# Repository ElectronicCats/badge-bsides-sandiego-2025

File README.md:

# Badge bsides San Diego 2025

## Technology

- CH32V003
- LEDs
- Display OLED
- 2x AAA Battery Holder
- Shitty Addon Connector

## Gratitude
Do you want to say thank you? Tag these companies on social networks and show them your badge, thanks to them it is possible

- [ElectronicCats](https://electroniccats.com/)
- [BsidesSanDiego](https://www.bsidessd.org/)

## License

Electronic Cats invests time and resources providing this open source design, please support Electronic Cats and open-source hardware by purchasing products from Electronic Cats!

Designed by Electronic Cats.

Hardware released under an CERN Open Hardware Licence v1.2. See the LICENSE_HARDWARE file for more information.

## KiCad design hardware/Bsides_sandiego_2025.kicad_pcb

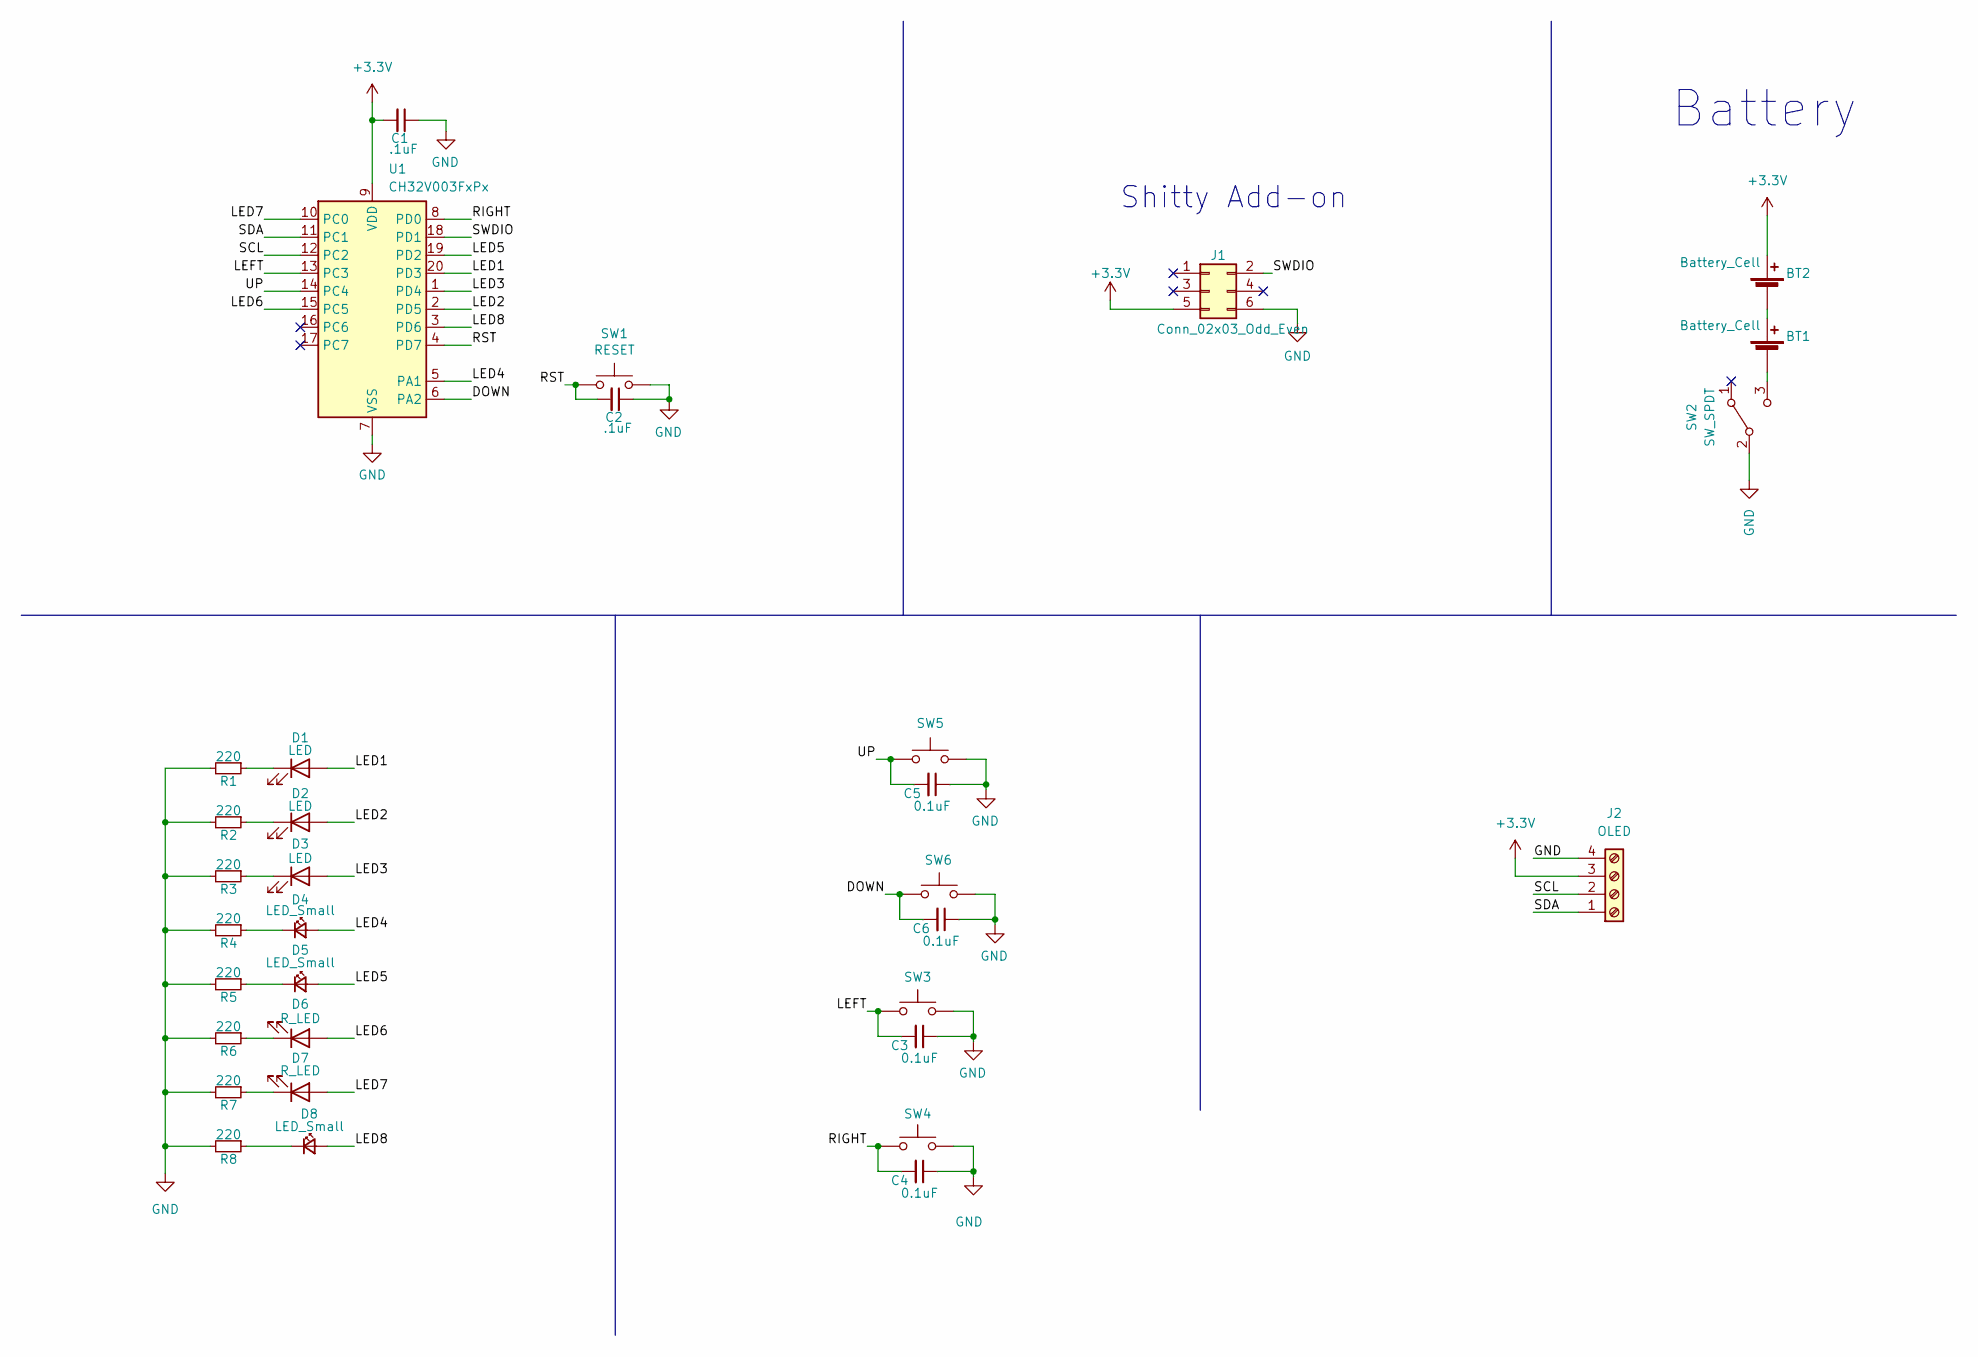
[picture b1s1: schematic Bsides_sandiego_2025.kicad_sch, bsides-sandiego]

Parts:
BT1, BT2: Battery_Cell; BatteryHolder_Keystone_2466_1xAAA; LCSC# C5290189
C1, C2: .1uF; C_0603_1608Metric; LCSC# C478888
C3, C4, C5, C6: 0.1uF; C_0603_1608Metric; LCSC# C478888
D1: LED; LED_0201_0603Metric; LCSC# C5440628
D2: LED; LED_0402_1005Metric; LCSC# C434450
D3: LED; LED_0603_1608Metric; LCSC# C434424
D4, D5: LED_Small; LED_S; LCSC# C2886268
D6, D7: R_LED; LYT77K-K2M1
D8: LED_Small; Led_S_S; LCSC# C409795
J1: Conn_02x03_Odd_Even; PinHeader_2x03_P2.54mm_Vertical_SMD; LCSC# C124390
J2: OLED; Display OLED 128 x32
R1, R2, R3, R4, R5, R6, R7, R8: 220; R_0603_1608Metric; LCSC# C22962
SW1: RESET; SW_SPST_TL3342; LCSC# C318889
SW2: SW_SPDT; MSK12C02; LCSC# C431540
SW3, SW4, SW5, SW6: SW_SPST_TL3342; LCSC# C318889
U1: CH32V003FxPx; TSSOP-20_4.4x6.5mm_P0.65mm; LCSC# C5187096

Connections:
+3.3V: BT2.2 (+), C1.2, J1.5, J2.3, U1.9 (VDD)
/DOWN: C6.2, SW6.2, U1.6 (PA2)
/LED1: D1.2 (A), U1.20 (PD3)
/LED2: D2.2 (A), U1.2 (PD5)
/LED3: D3.2 (A), U1.1 (PD4)
/LED4: D4.2 (A), U1.5 (PA1)
/LED5: D5.2 (A), U1.19 (PD2)
/LED6: D6.2 (A), U1.15 (PC5)
/LED7: D7.2 (A), U1.10 (PC0)
/LED8: D8.2 (A), U1.3 (PD6)
/LEFT: C3.2, SW3.2, U1.13 (PC3)
/RIGHT: C4.2, SW4.2, U1.8 (PD0)
/RST: C2.2, SW1.2, U1.4 (PD7)
/SCL: J2.2, U1.12 (PC2)
/SDA: J2.1, U1.11 (PC1)
/SWDIO: J1.2, U1.18 (PD1)
/UP: C5.2, SW5.2, U1.14 (PC4)
GND: C1.1, C2.1, C3.1, C4.1, C5.1, C6.1, J1.6, J2.4, R1.2, R2.2, R3.2, R4.2, R5.2, R6.2, R7.2, R8.2, SW1.1, SW2.2 (B), SW3.1, SW4.1, SW5.1, SW6.1, U1.7 (VSS)
unnamed: BT1.2 (+), BT2.1 (-)
unnamed: BT1.1 (-), SW2.3 (C)
unnamed: D1.1 (K), R1.1
unnamed: D2.1 (K), R2.1
unnamed: D3.1 (K), R3.1
unnamed: D4.1 (K), R4.1
unnamed: D5.1 (K), R5.1
unnamed: D6.1 (K), R6.1
unnamed: D7.1 (K), R7.1
unnamed: D8.1 (K), R8.1

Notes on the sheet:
Shitty Add-on
Battery

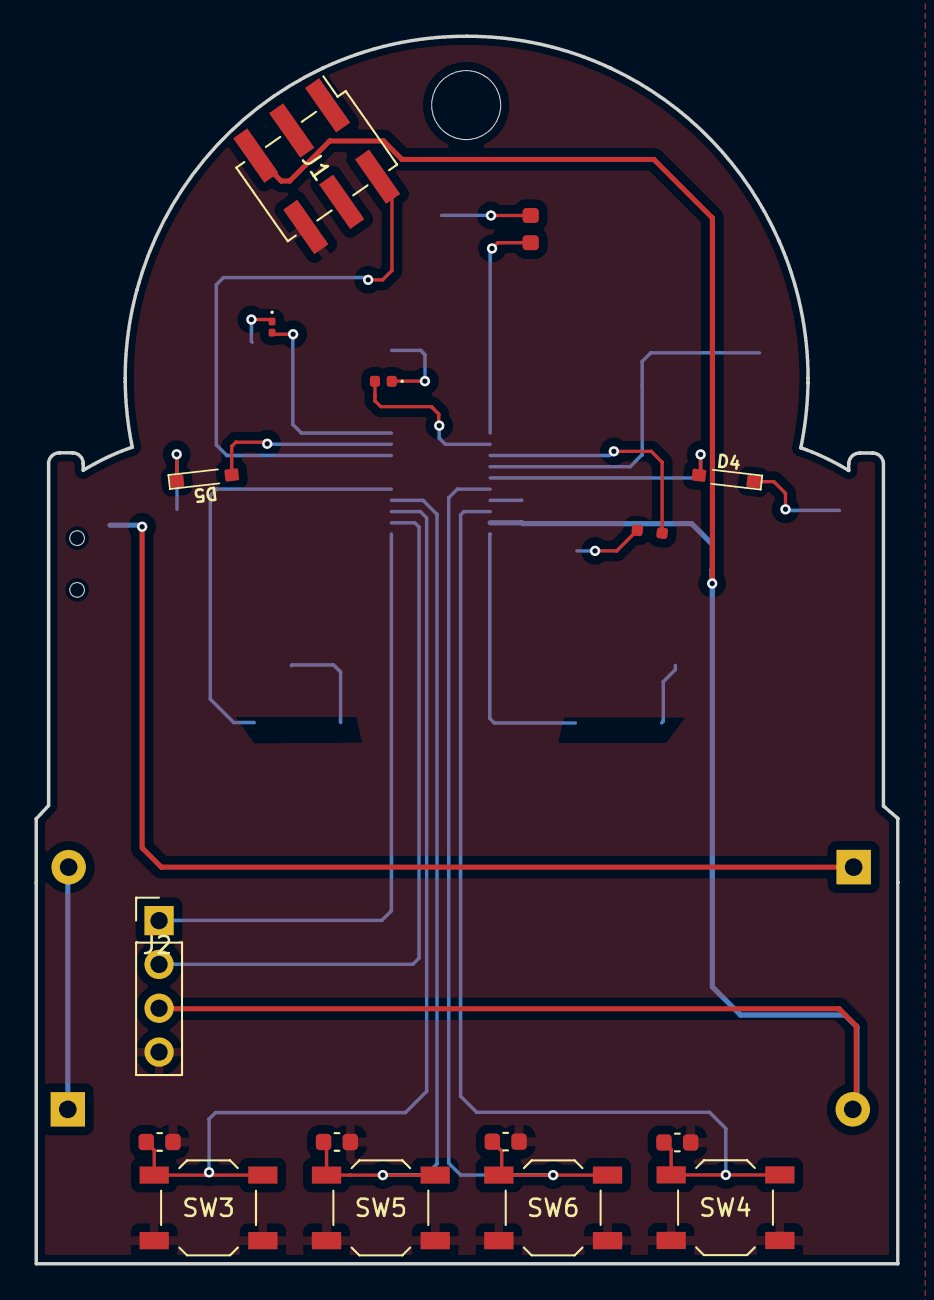
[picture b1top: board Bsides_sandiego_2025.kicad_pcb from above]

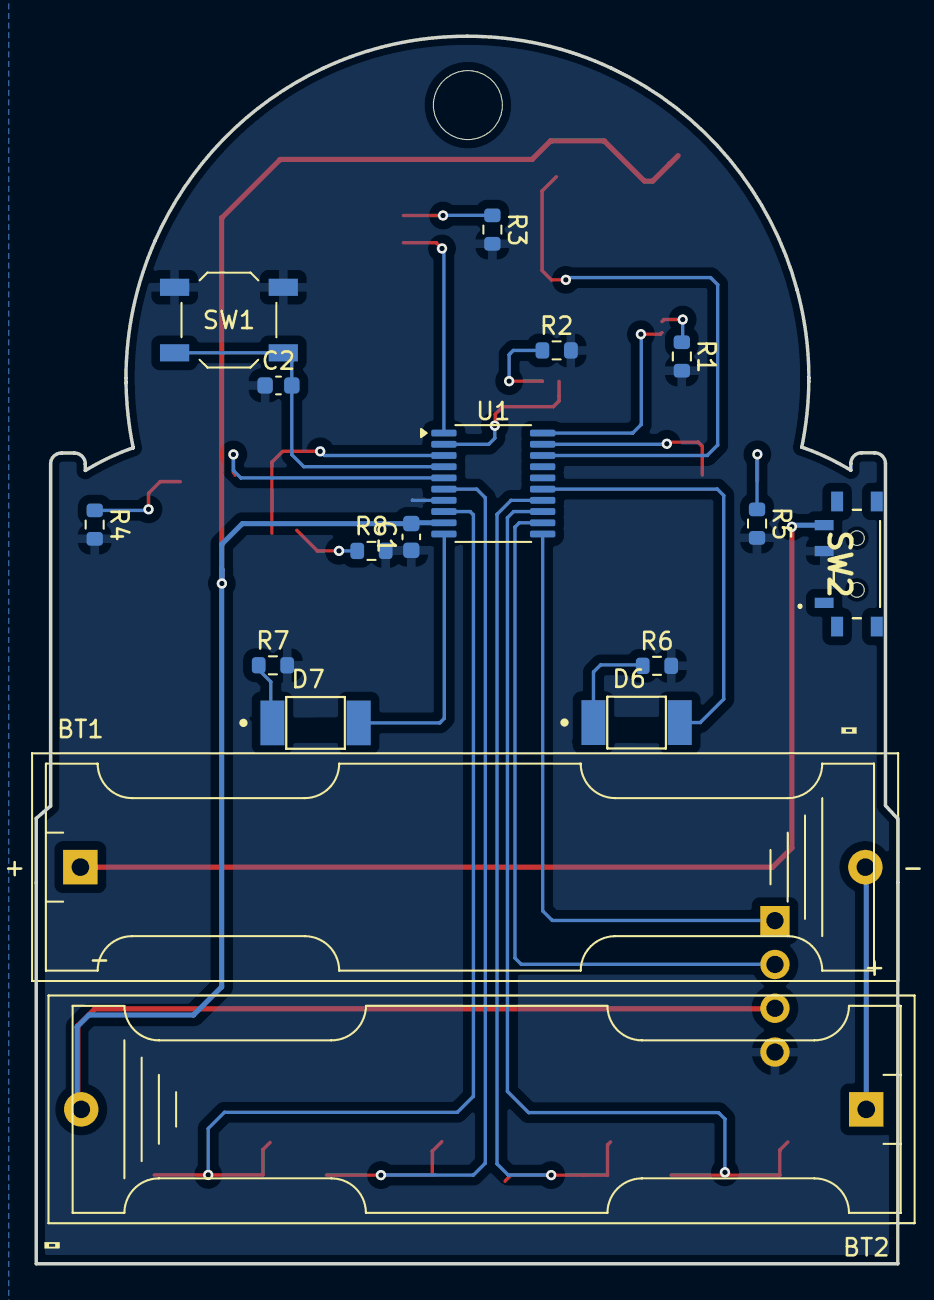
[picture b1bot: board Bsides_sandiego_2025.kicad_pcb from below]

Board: 2 copper layers, 49.9 x 71.2 mm, 36 parts (19 on the bottom side), 28 nets.

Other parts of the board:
Ref**: Val**; BAGDE BSIDES SAN DIEGO 25_30-10-24
kibuzzard-67607E30, kibuzzard-67607E30#2: G***; kibuzzard-67607E30

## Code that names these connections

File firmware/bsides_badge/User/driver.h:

// ===================================================================================
// Tiny Joypad Drivers for CH32V003                                           *
// v1.0 *
// ===================================================================================
//
// MCU abstraction layer.
// 2023 by Stefan Wagner:   https://github.com/wagiminator

#pragma once

#ifdef __cplusplus
extern "C" {
#endif

#include <stdbool.h>
#include "ch32v00x.h"
#include "gpio.h"
#include "oled_min.h"

// #define DEBUG_ENABLE 1
// #define DEV_VERSION 1

#define APP_DBG(X...)             \
  if (1) {                        \
    PRINT("[%s] ", __FUNCTION__); \
    PRINT(X);                     \
    PRINT("\r\n");                \
  }

// Pin assignments
#define BUTTON_RIGHT_PIN PD0
#define BUTTON_LEFT_PIN  PC3
#define BUTTON_UP_PIN    PC4
#ifdef DEV_VERSION
  #define BUTTON_DOWN_PIN PC6
#else
  #define BUTTON_DOWN_PIN PA2
#endif

#define LED1_PIN PD3
#define LED2_PIN PD5
#define LED3_PIN PD4
#define LED4_PIN PA1
#define LED5_PIN PD2
#define LED6_PIN PC5
#define LED7_PIN PC0
#define LED8_PIN PD6

#define PIN_SCL PC2  // pin connected to OLED (I2C SCL)
#define PIN_SDA PC1  // pin connected to OLED (I2C SDA)

// Delays
#define JOY_DLY_ms Delay_Ms
#define JOY_DLY_us Delay_Us

// Additional Defines
#define abs(n) ((n >= 0) ? (n) : (-(n)))

// Game slow-down delay
#define JOY_SLOWDOWN()  // DLY_ms(10)

extern uint8_t leds[];
extern uint8_t leds_count;

#define JOY_pad_pressed()  (ADC_read() > 10)
#define JOY_pad_released() (ADC_read() <= 10)

// static inline void JOY_init(void);
void JOY_init(void);

// OLED commands
#define JOY_OLED_init            OLED_init
#define JOY_OLED_end             I2C_stop
#define JOY_OLED_send(b)         I2C_write(b)
#define JOY_OLED_send_command(c) OLED_send_command(c)
#define JOY_OLED_data_start(y) \
  {                            \
    OLED_setpos(0, y);         \
    OLED_data_start();         \
  }

// Buttons
#define JOY_pad_pressed()  (ADC_read() > 10)
#define JOY_pad_released() (ADC_read() <= 10)

uint8_t joy_up_pressed(void);
uint8_t joy_down_pressed(void);
uint8_t joy_left_pressed(void);
uint8_t joy_right_pressed(void);
uint16_t JOY_random(void);
long map(long x, long in_min, long in_max, long out_min, long out_max);

#ifdef __cplusplus
};
#endif

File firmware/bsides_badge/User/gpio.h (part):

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// Basic GPIO Functions for CH32V003                                          * v1.6 *
// ===================================================================================
//
// Pins must be defined as PA0, PA1, .., PC0, PC1, etc. - e.g.:
// #define PIN_LED PC0      // LED on pin PC0
//
// PIN functions available:
// ------------------------
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// --------------------------------------------
// OPA_enable()             Enable OPA comparator
// OPA_disable()            Disable OPA comparator
// OPA_negative(PIN)        Set OPA inverting input PIN (PA1, PD0 only)
// OPA_positive(PIN)        Set OPA non-inverting input PIN (PA2, PD7 only)
// OPA_output()             Enable OPA output (push-pull) on pin PD4
// OPA_output_OD()          Enable OPA output (open-drain) on pin PD4
// OPA_read()               Read OPA output (0: pos < neg, 1: pos > neg)
//
// Notes:
// ------
// - (*) default state
// - For interrupts and events: Each PIN number can only be used once simultaneously.
//   (For example, PA1 and PC1 cannot be used simultaneously, but PA1 and PC2).
// - Pins used for ADC must be set with PIN_input_AN beforehand. Only the following 
//   pins can be used as INPUT for the ADC: PA1, PA2, PC4, PD2, PD3, PD4, PD5, PD6.
// - Pins used as input for OPA comparator must be set with PIN_input_AN beforehand.
//   Only the following pins can be used for the OPA: PA1 or PD0 as negative
//   (inverting) input, PA2 or PD7 as positive (non-inverting) input and PD4 as
//   ouput.
//
// 2023 by Stefan Wagner:   https://github.com/wagiminator
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// ===================================================================================
// Enumerate PIN designators (use these designators to define pins)
// ===================================================================================
enum{ PA0, PA1, PA2, PA3, PA4, PA5, PA6, PA7,
      PC0, PC1, PC2, PC3, PC4, PC5, PC6, PC7,
      PD0, PD1, PD2, PD3, PD4, PD5, PD6, PD7};

// ===================================================================================
// Set PIN as INPUT (high impedance, no pullup/pulldown)
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  ((PIN>=PA0)&&(PIN<=PA7) ? ( GPIOA->CFGLR =  (GPIOA->CFGLR                          \
                                           & ~((uint32_t)0b1111<<(((PIN)&7)<<2)))    \
                                           |  ((uint32_t)0b0100<<(((PIN)&7)<<2)) ) : \
  ((PIN>=PC0)&&(PIN<=PC7) ? ( GPIOC->CFGLR =  (GPIOC->CFGLR                          \
                                           & ~((uint32_t)0b1111<<(((PIN)&7)<<2)))    \
                                           |  ((uint32_t)0b0100<<(((PIN)&7)<<2)) ) : \
  ((PIN>=PD0)&&(PIN<=PD7) ? ( GPIOD->CFGLR =  (GPIOD->CFGLR                          \
                                           & ~((uint32_t)0b1111<<(((PIN)&7)<<2)))    \
                                           |  ((uint32_t)0b0100<<(((PIN)&7)<<2)) ) : \
(0))))
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                                            & ~((uint32_t)0b1111<<(((PIN)&7)<<2)))   \
                                            |  ((uint32_t)0b1000<<(((PIN)&7)<<2));   \
                              GPIOA->BSHR   =  ((uint32_t)1<<((PIN)&7));        }) : \
  ((PIN>=PC0)&&(PIN<=PC7) ? ({GPIOC->CFGLR  =  (GPIOC->CFGLR                         \
                                            & ~((uint32_t)0b1111<<(((PIN)&7)<<2)))   \
                                            |  ((uint32_t)0b1000<<(((PIN)&7)<<2));   \
                              GPIOC->BSHR   =  ((uint32_t)1<<((PIN)&7));        }) : \
  ((PIN>=PD0)&&(PIN<=PD7) ? ({GPIOD->CFGLR  =  (GPIOD->CFGLR                         \
                                            & ~((uint32_t)0b1111<<(((PIN)&7)<<2)))   \
                                            |  ((uint32_t)0b1000<<(((PIN)&7)<<2));   \
                              GPIOD->BSHR   =  ((uint32_t)1<<((PIN)&7));        }) : \
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                                            & ~((uint32_t)0b1111<<(((PIN)&7)<<2)))   \
                                            |  ((uint32_t)0b1000<<(((PIN)&7)<<2));   \
                              GPIOA->BCR    =  ((uint32_t)1<<((PIN)&7));        }) : \
  ((PIN>=PC0)&&(PIN<=PC7) ? ({GPIOC->CFGLR  =  (GPIOC->CFGLR                         \
                                            & ~((uint32_t)0b1111<<(((PIN)&7)<<2)))   \
                                            |  ((uint32_t)0b1000<<(((PIN)&7)<<2));   \
                              GPIOC->BCR    =  ((uint32_t)1<<((PIN)&7));        }) : \
  ((PIN>=PD0)&&(PIN<=PD7) ? ({GPIOD->CFGLR  =  (GPIOD->CFGLR                         \
                                            & ~((uint32_t)0b1111<<(((PIN)&7)<<2)))   \
                                            |  ((uint32_t)0b1000<<(((PIN)&7)<<2));   \
                              GPIOD->BCR    =  ((uint32_t)1<<((PIN)&7));        }) : \
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// ===================================================================================
#define PIN_input_AN(PIN) \
  ((PIN>=PA0)&&(PIN<=PA7) ? ( GPIOA->CFGLR &= ~((uint32_t)0b1111<<(((PIN)&7)<<2)) ) : \
  ((PIN>=PC0)&&(PIN<=PC7) ? ( GPIOC->CFGLR &= ~((uint32_t)0b1111<<(((PIN)&7)<<2)) ) : \
  ((PIN>=PD0)&&(PIN<=PD7) ? ( GPIOD->CFGLR &= ~((uint32_t)0b1111<<(((PIN)&7)<<2)) ) : \
(0))))
#define PIN_input_AD  PIN_input_AN
#define PIN_input_ADC PIN_input_AN
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  ((PIN>=PA0)&&(PIN<=PA7) ? ( GPIOA->CFGLR =  (GPIOA->CFGLR                          \
                                           & ~((uint32_t)0b1111<<(((PIN)&7)<<2)))    \
                                           |  ((uint32_t)0b0001<<(((PIN)&7)<<2)) ) : \
  ((PIN>=PC0)&&(PIN<=PC7) ? ( GPIOC->CFGLR =  (GPIOC->CFGLR                          \
                                           & ~((uint32_t)0b1111<<(((PIN)&7)<<2)))    \
                                           |  ((uint32_t)0b0001<<(((PIN)&7)<<2)) ) : \
  ((PIN>=PD0)&&(PIN<=PD7) ? ( GPIOD->CFGLR =  (GPIOD->CFGLR                          \
                                           & ~((uint32_t)0b1111<<(((PIN)&7)<<2)))    \
                                           |  ((uint32_t)0b0001<<(((PIN)&7)<<2)) ) : \
(0))))
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  ((PIN>=PA0)&&(PIN<=PA7) ? ( GPIOA->CFGLR =  (GPIOA->CFGLR                          \
                                           & ~((uint32_t)0b1111<<(((PIN)&7)<<2)))    \
                                           |  ((uint32_t)0b0101<<(((PIN)&7)<<2)) ) : \
  ((PIN>=PC0)&&(PIN<=PC7) ? ( GPIOC->CFGLR =  (GPIOC->CFGLR                          \
                                           & ~((uint32_t)0b1111<<(((PIN)&7)<<2)))    \
                                           |  ((uint32_t)0b0101<<(((PIN)&7)<<2)) ) : \
  ((PIN>=PD0)&&(PIN<=PD7) ? ( GPIOD->CFGLR =  (GPIOD->CFGLR                          \
                                           & ~((uint32_t)0b1111<<(((PIN)&7)<<2)))    \
                                           |  ((uint32_t)0b0101<<(((PIN)&7)<<2)) ) : \
(0))))
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  ((PIN>=PA0)&&(PIN<=PA7) ? ( GPIOA->CFGLR =  (GPIOA->CFGLR                          \
                                           & ~((uint32_t)0b1111<<(((PIN)&7)<<2)))    \
                                           |  ((uint32_t)0b1001<<(((PIN)&7)<<2)) ) : \
  ((PIN>=PC0)&&(PIN<=PC7) ? ( GPIOC->CFGLR =  (GPIOC->CFGLR                          \
                                           & ~((uint32_t)0b1111<<(((PIN)&7)<<2)))    \
                                           |  ((uint32_t)0b1001<<(((PIN)&7)<<2)) ) : \
  ((PIN>=PD0)&&(PIN<=PD7) ? ( GPIOD->CFGLR =  (GPIOD->CFGLR                          \
                                           & ~((uint32_t)0b1111<<(((PIN)&7)<<2)))    \
                                           |  ((uint32_t)0b1001<<(((PIN)&7)<<2)) ) : \
(0))))
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  ((PIN>=PA0)&&(PIN<=PA7) ? ( GPIOA->CFGLR =  (GPIOA->CFGLR                          \
                                           & ~((uint32_t)0b1111<<(((PIN)&7)<<2)))    \
                                           |  ((uint32_t)0b1101<<(((PIN)&7)<<2)) ) : \
  ((PIN>=PC0)&&(PIN<=PC7) ? ( GPIOC->CFGLR =  (GPIOC->CFGLR                          \
                                           & ~((uint32_t)0b1111<<(((PIN)&7)<<2)))    \
                                           |  ((uint32_t)0b1101<<(((PIN)&7)<<2)) ) : \
  ((PIN>=PD0)&&(PIN<=PD7) ? ( GPIOD->CFGLR =  (GPIOD->CFGLR                          \
                                           & ~((uint32_t)0b1111<<(((PIN)&7)<<2)))    \
                                           |  ((uint32_t)0b1101<<(((PIN)&7)<<2)) ) : \
(0))))
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// ===================================================================================
#define PIN_low(PIN) \
  ((PIN>=PA0)&&(PIN<=PA7) ? ( GPIOA->BCR = 1<<((PIN)&7) ) : \
  ((PIN>=PC0)&&(PIN<=PC7) ? ( GPIOC->BCR = 1<<((PIN)&7) ) : \
  ((PIN>=PD0)&&(PIN<=PD7) ? ( GPIOD->BCR = 1<<((PIN)&7) ) : \
(0))))

// ===================================================================================
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// ===================================================================================
#define PIN_high(PIN) \
  ((PIN>=PA0)&&(PIN<=PA7) ? ( GPIOA->BSHR = 1<<((PIN)&7) ) : \
  ((PIN>=PC0)&&(PIN<=PC7) ? ( GPIOC->BSHR = 1<<((PIN)&7) ) : \
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
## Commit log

2024-10-30 feat(Hw):Init_Schematic_And_PCB
2024-12-13 feat(Hw):Update_PCB_And_Floorplan
2024-12-13 feat(Hw):Update_Route
2024-12-13 feat(Hw):Update_BOM
2024-12-16 feat(Hw):Update_Batt_Holder
2024-12-16 feat(Hw):Update_csv_And_Size
2024-12-16 feat(Hw):Update_Add_On_Connector
2025-01-07 feat: add base project
2025-01-07 feat: add display test
2025-01-07 chore: add config files
2025-01-07 feat: add tetris game
2025-01-07 fix(Hw):Update_J1_PartN.
2025-01-12 feat: add resources of bsides logo
2025-01-12 chore: add clan format and pre commit config files
2025-01-13 feat: remap buttons
2025-01-14 fix: gpio pins initialization
2025-01-14 feat: add leds animation at startup
2025-01-15 feat: display logo at startup
2025-01-16 feat: save reboot counter on flash
2025-01-16 refactor: separate game logic
2025-01-16 refactor: ssd1306 params order
2025-01-16 feat: add hardware tests
2025-01-20 feat: add bitmaps of menus
2025-01-22 fix: pa port init
2025-01-22 feat: add menus and game
2025-01-22 feat: reduce font size from 984 to 208 bytes
2025-01-22 feat: add credits text
2025-01-22 feat: get user nickname
2025-01-22 refactor: remove unused libraries
2025-01-24 feat: reduce buttons sensibilitiy on game
2025-01-24 fix: repeated clicks while inserting nickname
2025-01-24 feat: add menus with icons
2025-01-28 feat: change nickname menu by leds menu icon
2025-01-28 feat: add leds control
2025-01-29 fix: reduce buttons sensibilty
2025-01-29 feat: turn leds off inside menus
2025-01-29 feat: disable dev version by default
2025-01-29 feat: Create LICENSE_HARDWARE.md
2025-01-29 docs:Update README.md
2025-01-29 Fix: Update README.md
